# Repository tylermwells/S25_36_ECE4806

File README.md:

# S25-36-ECE4806
This is a repository to collaborate with schematic drawings, information, etc.

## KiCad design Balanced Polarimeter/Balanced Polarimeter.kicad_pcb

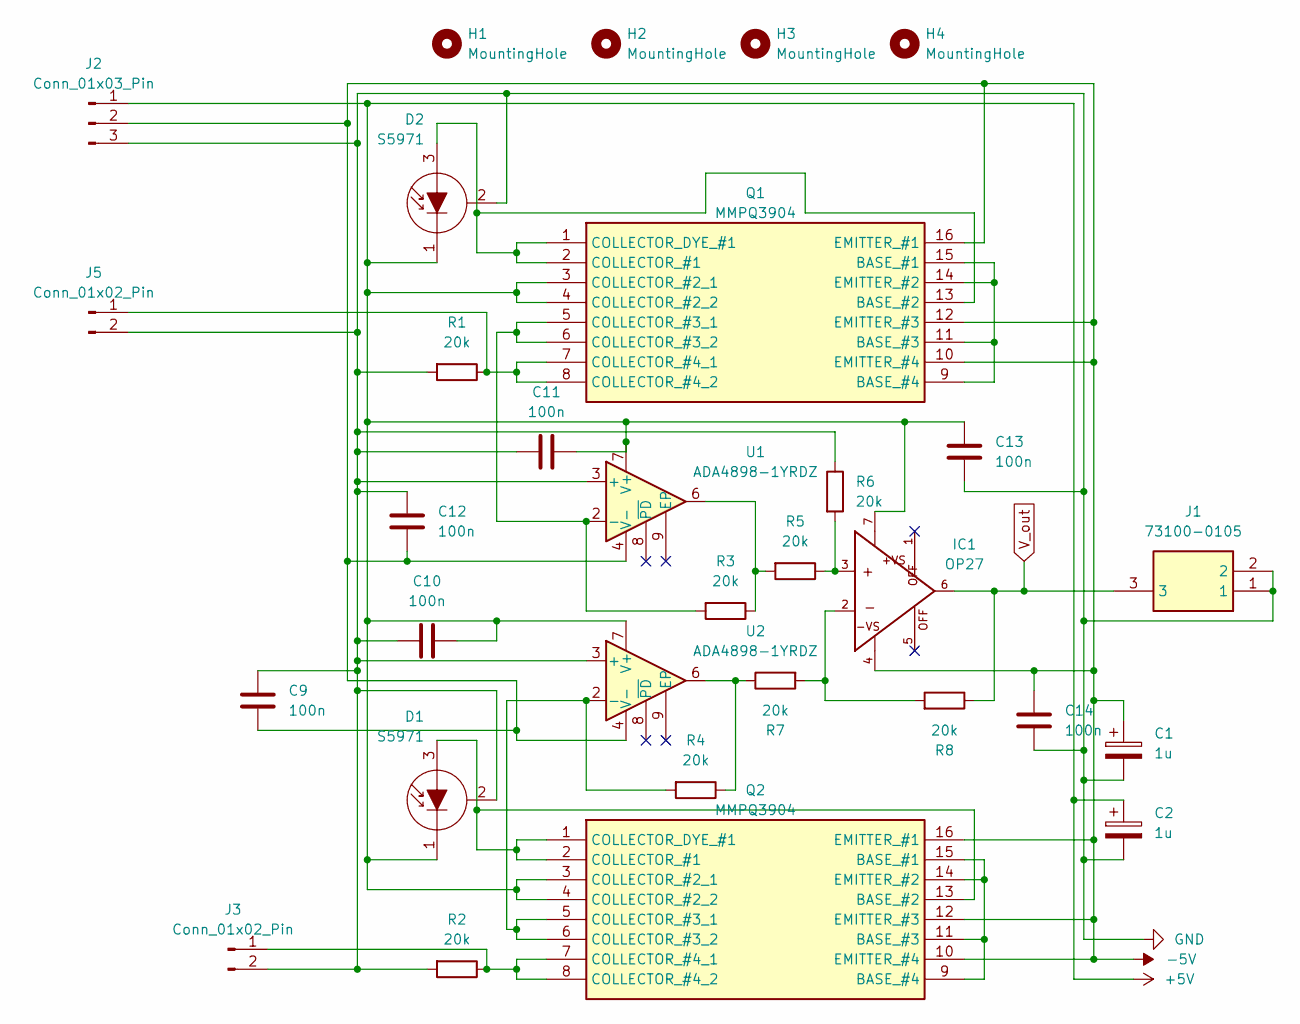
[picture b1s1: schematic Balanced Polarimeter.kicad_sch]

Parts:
C1, C2: 1u; CP_Radial_D5.0mm_P2.50mm
C9, C10, C11, C12, C13, C14: 100n; C_Disc_D3.0mm_W1.6mm_P2.50mm
D1, D2: S5971; TO-18-3
H1, H2, H3, H4: MountingHole; MountingHole_2.1mm
IC1: OP27; DIL08
J1: 73100-0105; Mouser Part Number 538-73100-0105
J2: Conn_01x03_Pin; FanPinHeader_1x03_P2.54mm_Vertical
J3, J5: Conn_01x02_Pin; PinHeader_1x02_P2.54mm_Vertical
Q1, Q2: MMPQ3904; SOIC127P600X175-16N; Mouser Part Number 512-MMPQ3904
R1, R2, R3, R4, R5, R6, R7, R8: 20k; R_Axial_DIN0207_L6.3mm_D2.5mm_P10.16mm_Horizontal
U1, U2: ADA4898-1YRDZ; SOIC-8-1EP_3.9x4.9mm_P1.27mm_EP2.29x3mm

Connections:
+5V: C2.1, C10.1, C11.1, C13.1, D1.1 (K), D2.1 (K), IC1.7, J2.1, Q1.3 (COLLECTOR_#2_1), Q1.4 (COLLECTOR_#2_2), Q2.3 (COLLECTOR_#2_1), Q2.4 (COLLECTOR_#2_2), U1.7 (V+), U2.7 (V+)
-5V: C1.1, C9.2, C12.2, C14.1, IC1.4, J2.2, Q1.10 (EMITTER_#4), Q1.12 (EMITTER_#3), Q1.16 (EMITTER_#1), Q2.10 (EMITTER_#4), Q2.12 (EMITTER_#3), Q2.16 (EMITTER_#1), U1.4 (V-), U2.4 (V-)
GND: C1.2, C2.2, C9.1, C10.2, C11.2, C12.1, C13.2, C14.2, D1.2 (C), D2.2 (C), J1.1, J1.2, J2.3, J3.2, J5.2, R1.2, R2.2, R6.1, U1.3 (+), U2.3 (+)
unnamed: D1.3 (A), Q2.1 (COLLECTOR_DYE_#1), Q2.2 (COLLECTOR_#1), Q2.13 (BASE_#2)
unnamed: D2.3 (A), Q1.1 (COLLECTOR_DYE_#1), Q1.2 (COLLECTOR_#1), Q1.13 (BASE_#2)
unnamed: IC1.2, R7.2, R8.2
unnamed: IC1.3, R5.1, R6.2
unnamed: J3.1, Q2.7 (COLLECTOR_#4_1), Q2.8 (COLLECTOR_#4_2), R2.1
unnamed: J5.1, Q1.7 (COLLECTOR_#4_1), Q1.8 (COLLECTOR_#4_2), R1.1
unnamed: Q1.9 (BASE_#4), Q1.11 (BASE_#3), Q1.14 (EMITTER_#2), Q1.15 (BASE_#1)
unnamed: Q1.5 (COLLECTOR_#3_1), Q1.6 (COLLECTOR_#3_2), R3.2, U1.2 (-)
unnamed: Q2.9 (BASE_#4), Q2.11 (BASE_#3), Q2.14 (EMITTER_#2), Q2.15 (BASE_#1)
unnamed: Q2.5 (COLLECTOR_#3_1), Q2.6 (COLLECTOR_#3_2), R4.2, U2.2 (-)
unnamed: R3.1, R5.2, U1.6
unnamed: R4.1, R7.1, U2.6
V_out: IC1.6, J1.3, R8.1

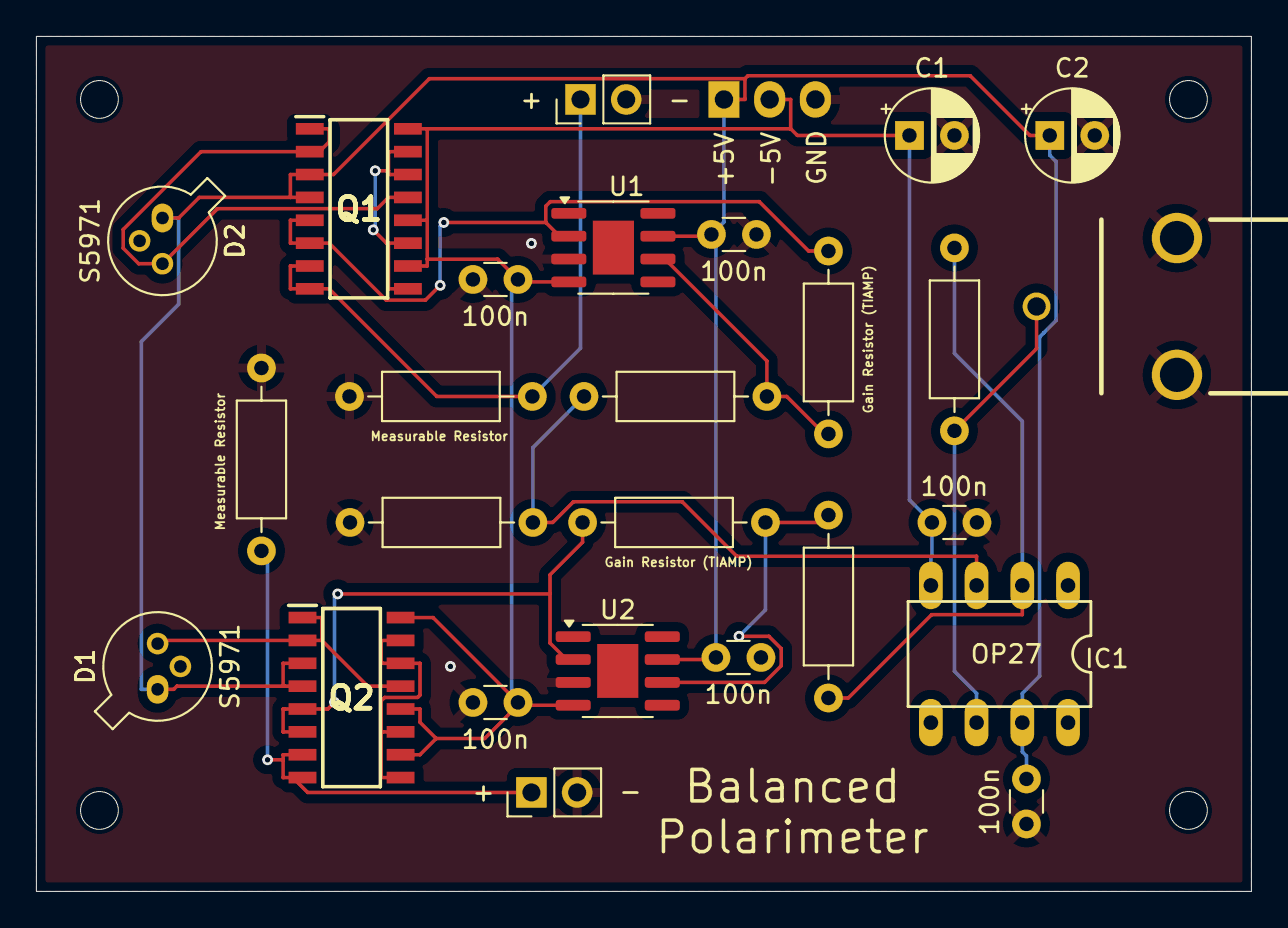
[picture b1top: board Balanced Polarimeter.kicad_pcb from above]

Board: 2 copper layers, 67.5 x 47.5 mm, 31 parts (0 on the bottom side), 16 nets.

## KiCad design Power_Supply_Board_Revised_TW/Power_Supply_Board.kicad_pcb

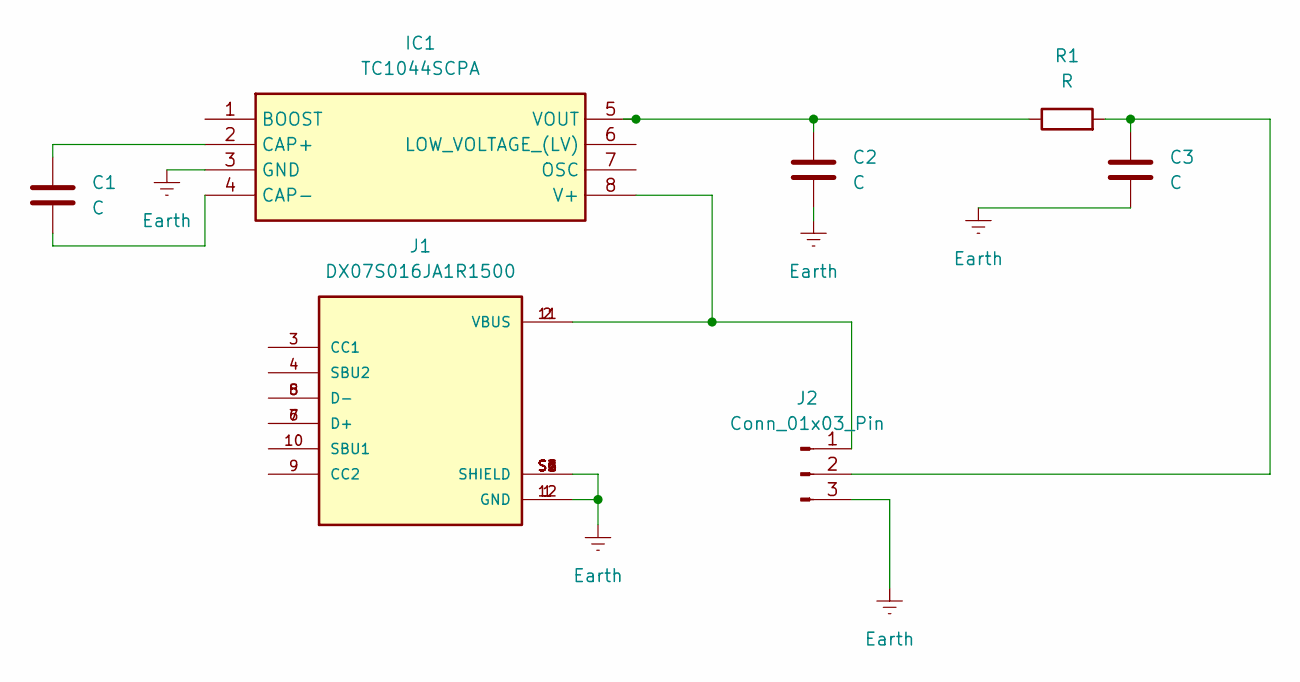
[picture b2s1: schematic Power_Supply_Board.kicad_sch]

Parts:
C1, C2: C; C_Rect_L7.0mm_W6.0mm_P5.00mm
C3: C; C_Rect_L16.5mm_W11.8mm_P15.00mm_MKT
IC1: TC1044SCPA; DIP762W56P254L950H508Q8N; Mouser Part Number 579-TC1044SCPA
J1: DX07S016JA1R1500; JAE_DX07S016JA1R1500; PARTREV 1
J2: Conn_01x03_Pin; PinHeader_1x03_P2.54mm_Vertical
R1: R; R_Axial_DIN0207_L6.3mm_D2.5mm_P10.16mm_Horizontal

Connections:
Earth: C2.2, C3.2, IC1.3 (GND), J1.1 (GND), J1.12 (GND), J1.S1 (SHIELD), J1.S2 (SHIELD), J1.S3 (SHIELD), J1.S4 (SHIELD), J1.S5 (SHIELD), J1.S6 (SHIELD), J2.3
unnamed: C1.1, IC1.2 (CAP+)
unnamed: C1.2, IC1.4 (CAP-)
unnamed: IC1.8 (V+), J1.2 (VBUS), J1.11 (VBUS), J2.1
unnamed: C2.1, IC1.5 (VOUT), R1.1
unnamed: J1.6 (D+), J1.7 (D+)
unnamed: J1.5 (D-), J1.8 (D-)
unnamed: C3.1, J2.2, R1.2

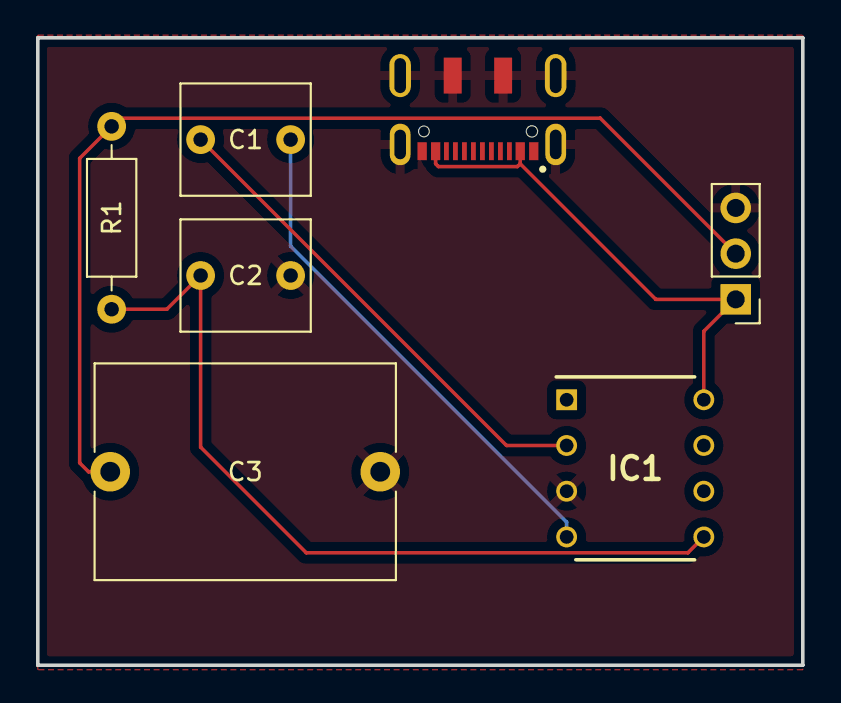
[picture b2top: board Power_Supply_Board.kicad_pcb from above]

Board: 2 copper layers, 42.5 x 34.9 mm, 7 parts (0 on the bottom side), 8 nets.

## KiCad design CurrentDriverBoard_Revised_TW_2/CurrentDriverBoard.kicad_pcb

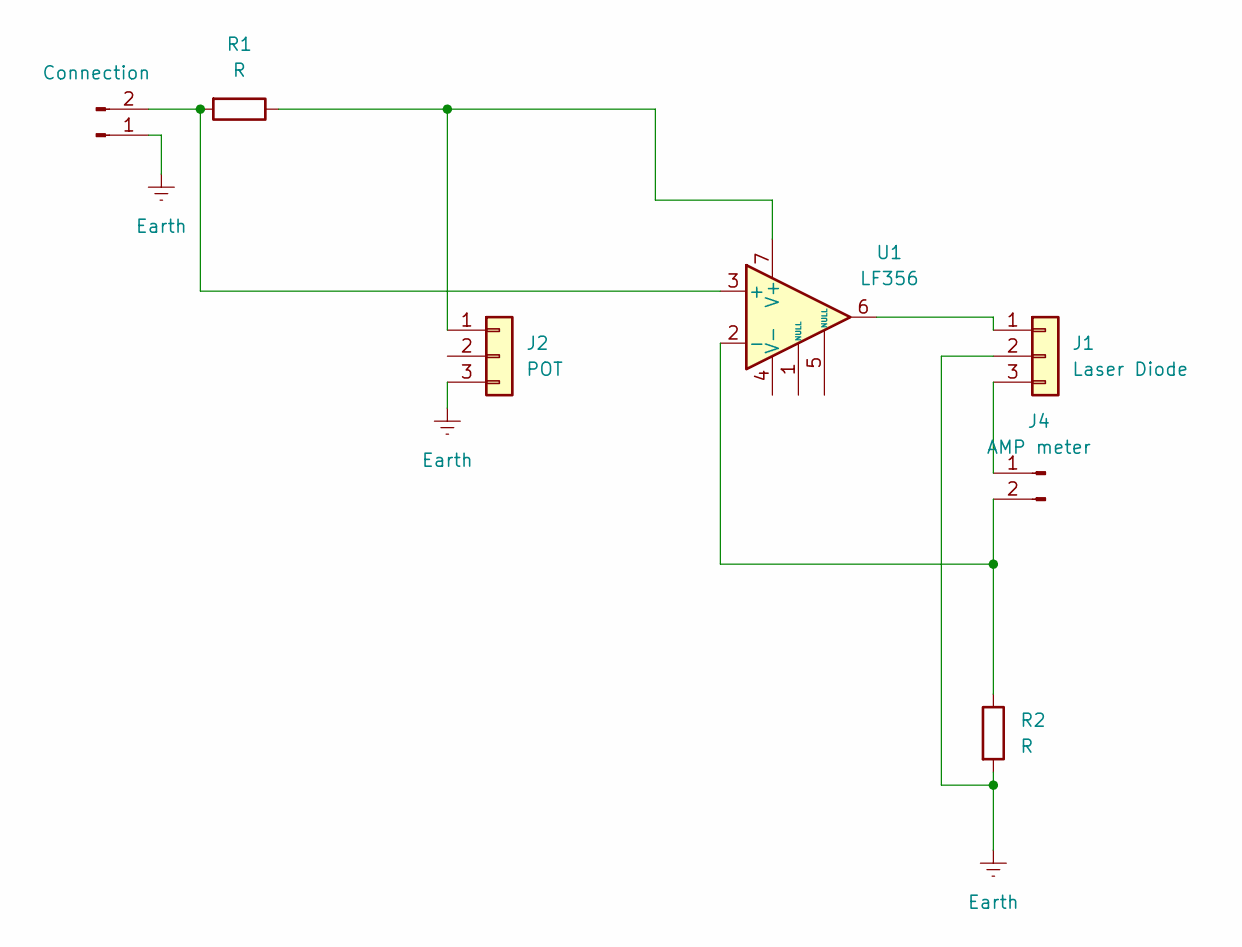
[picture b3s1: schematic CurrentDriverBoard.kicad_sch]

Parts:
J1: Laser Diode; PinHeader_1x03_P2.54mm_Vertical
J2: POT; PinHeader_1x03_P2.54mm_Vertical
J3: Connection; PinHeader_1x02_P2.54mm_Vertical
J4: AMP meter; PinHeader_1x02_P2.54mm_Vertical
R1, R2: R; R_Axial_DIN0207_L6.3mm_D2.5mm_P10.16mm_Horizontal
U1: LF356; DIP794W53P254L959H508Q8N

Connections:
Earth: J1.2, J2.3, J3.1, R2.2
unnamed: J1.1, U1.6
unnamed: J1.3, J4.1
unnamed: J2.1, R1.1, U1.7 (V+)
unnamed: J3.2, R1.2, U1.3 (+)
unnamed: J4.2, R2.1, U1.2 (-)

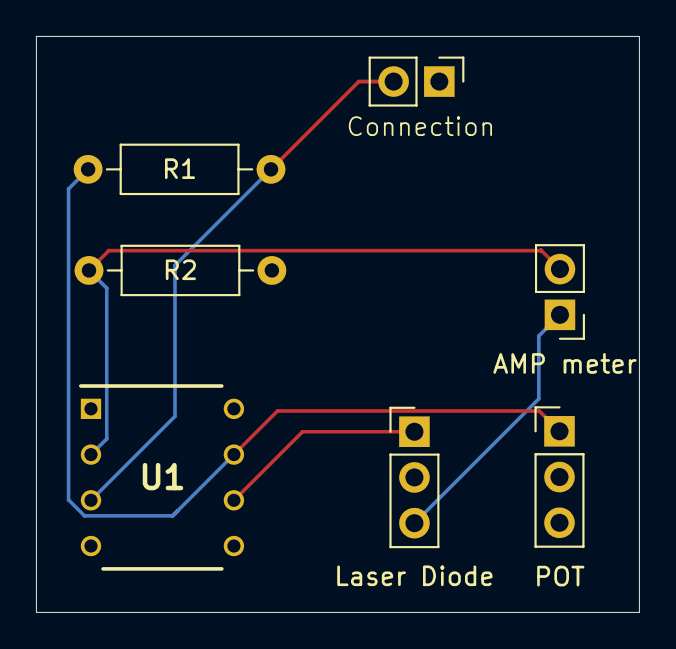
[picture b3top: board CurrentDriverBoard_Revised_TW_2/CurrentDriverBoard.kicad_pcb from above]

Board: 2 copper layers, 33.5 x 32.0 mm, 7 parts (0 on the bottom side), 6 nets.

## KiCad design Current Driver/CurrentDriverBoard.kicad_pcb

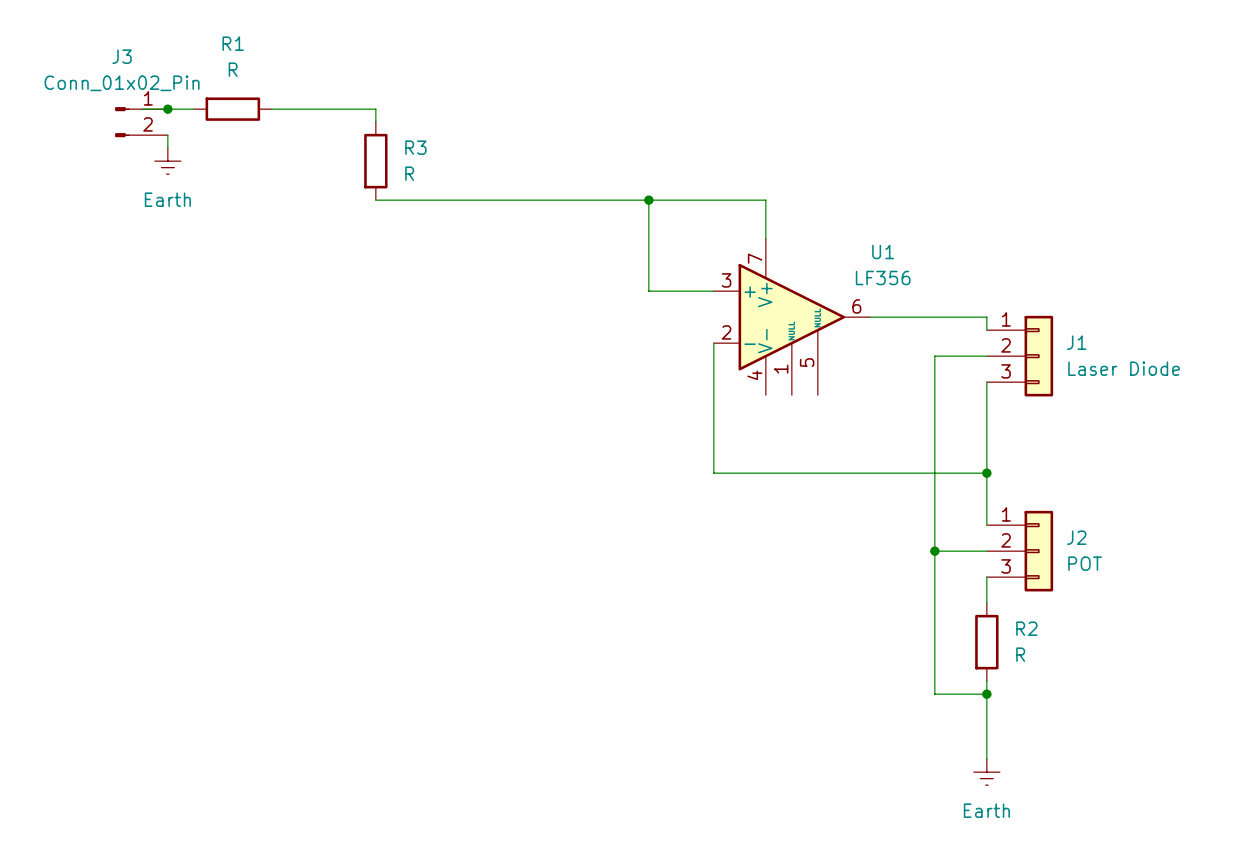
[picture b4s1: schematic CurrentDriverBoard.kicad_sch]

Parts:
J1: Laser Diode; PinHeader_1x03_P2.54mm_Vertical
J2: POT; PinHeader_1x03_P2.54mm_Vertical
J3: Conn_01x02_Pin; PinHeader_1x02_P2.54mm_Vertical
R1, R2, R3: R; R_Axial_DIN0207_L6.3mm_D2.5mm_P10.16mm_Horizontal
U1: LF356; DIP794W53P254L959H508Q8N

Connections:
Earth: J1.2, J2.2, J3.2, R2.2
unnamed: J1.1, U1.6
unnamed: J1.3, J2.1, U1.2 (-)
unnamed: J2.3, R2.1
unnamed: J3.1, R1.2
unnamed: R1.1, R3.1
unnamed: R3.2, U1.3 (+), U1.7 (V+)

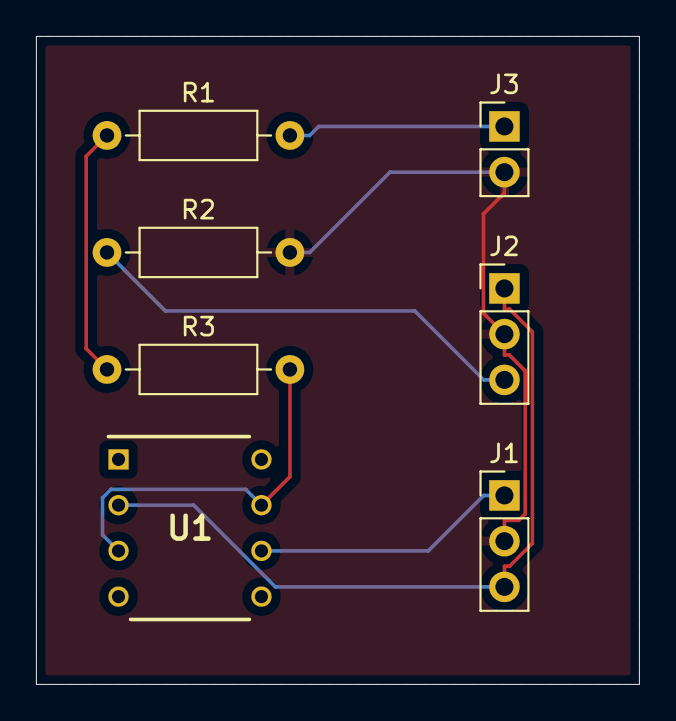
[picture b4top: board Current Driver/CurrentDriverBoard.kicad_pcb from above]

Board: 2 copper layers, 33.5 x 36.0 mm, 7 parts (0 on the bottom side), 7 nets.

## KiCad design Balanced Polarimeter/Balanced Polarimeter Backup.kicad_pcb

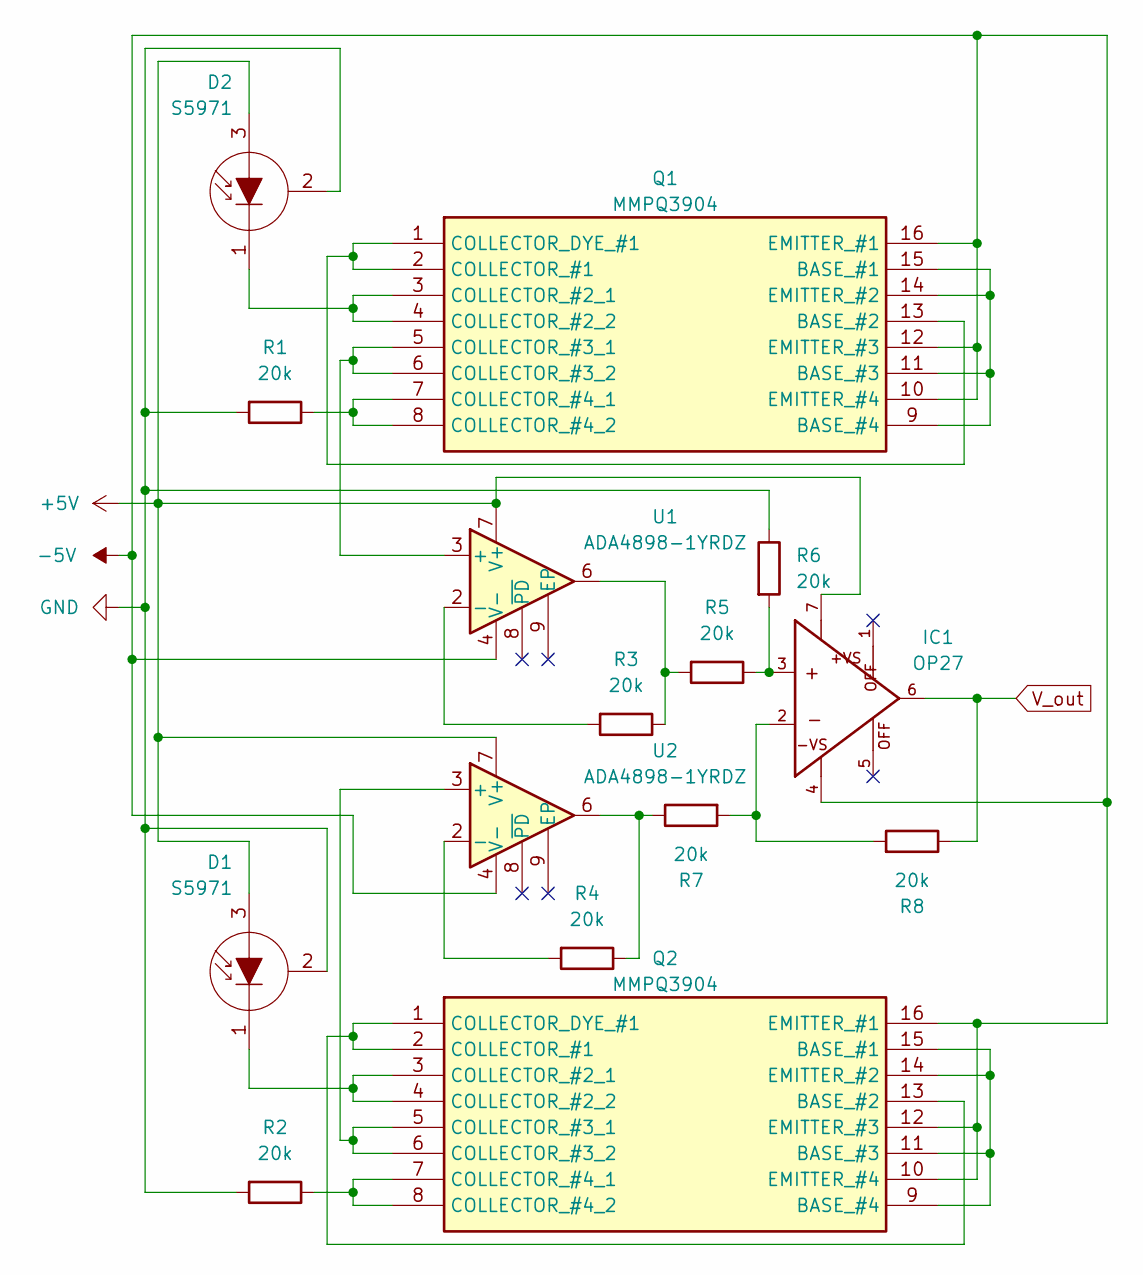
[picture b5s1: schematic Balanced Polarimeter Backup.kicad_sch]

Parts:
D1, D2: S5971; TO-18-3
IC1: OP27; DIL08
Q1, Q2: MMPQ3904; SOIC127P600X175-16N; Mouser Part Number 512-MMPQ3904
R1, R2, R3, R4, R5, R6, R7, R8: 20k; R_Axial_DIN0207_L6.3mm_D2.5mm_P10.16mm_Horizontal
U1, U2: ADA4898-1YRDZ; SOIC-8-1EP_3.9x4.9mm_P1.27mm_EP2.29x3mm

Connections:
+5V: D1.3 (A), D2.3 (A), IC1.7, U1.7 (V+), U2.7 (V+)
-5V: IC1.4, Q1.10 (EMITTER_#4), Q1.12 (EMITTER_#3), Q1.16 (EMITTER_#1), Q2.10 (EMITTER_#4), Q2.12 (EMITTER_#3), Q2.16 (EMITTER_#1), U1.4 (V-), U2.4 (V-)
GND: D1.2 (C), D2.2 (C), R1.2, R2.2, R6.1
unnamed: D1.1 (K), Q2.3 (COLLECTOR_#2_1), Q2.4 (COLLECTOR_#2_2)
unnamed: D2.1 (K), Q1.3 (COLLECTOR_#2_1), Q1.4 (COLLECTOR_#2_2)
unnamed: IC1.2, R7.2, R8.2
unnamed: IC1.3, R5.1, R6.2
unnamed: Q1.9 (BASE_#4), Q1.11 (BASE_#3), Q1.14 (EMITTER_#2), Q1.15 (BASE_#1)
unnamed: Q1.1 (COLLECTOR_DYE_#1), Q1.2 (COLLECTOR_#1), Q1.13 (BASE_#2)
unnamed: Q1.5 (COLLECTOR_#3_1), Q1.6 (COLLECTOR_#3_2), U1.3 (+)
unnamed: Q1.7 (COLLECTOR_#4_1), Q1.8 (COLLECTOR_#4_2), R1.1
unnamed: Q2.9 (BASE_#4), Q2.11 (BASE_#3), Q2.14 (EMITTER_#2), Q2.15 (BASE_#1)
unnamed: Q2.1 (COLLECTOR_DYE_#1), Q2.2 (COLLECTOR_#1), Q2.13 (BASE_#2)
unnamed: Q2.5 (COLLECTOR_#3_1), Q2.6 (COLLECTOR_#3_2), U2.3 (+)
unnamed: Q2.7 (COLLECTOR_#4_1), Q2.8 (COLLECTOR_#4_2), R2.1
unnamed: R3.1, R5.2, U1.6
unnamed: R4.1, R7.1, U2.6
unnamed: R3.2, U1.2 (-)
unnamed: R4.2, U2.2 (-)
V_out: IC1.6, R8.1

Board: 2 copper layers, 15 parts (0 on the bottom side), 20 nets, no tracks yet.

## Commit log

2025-01-10 Adding LTSPICE Folder with schematic
2025-01-10 Balanced Polarimeter
    Created the balanced polarimeter project folder for PCB
2025-01-10 Balanced Polarimeter
2025-01-21 Added SS and TA
2025-01-23 Next revision
    Rewired all powers to a single node and swapped the op amp for an op27
2025-01-23 PCB Start Design
    Edited the naming of some components and created a PCB to layout. It's still missing the BNC connector for now
2025-01-23 Cleanup
    Removed the "Backup" files
2025-01-24 Added BNC
2025-01-24 Simple Updates
2025-01-30 Added GND Layer and 2mm Mount Holes
2025-01-30 Added Part List
2025-01-31 Updating Parts List
    Updating Parts List with links of what we need
2025-01-31 Adding AJs current driver to the repository
2025-02-03 Adding Power Supply Driver and Master Parts list to the repository. More updates to come soon because we need to add resistors.
2025-02-03 Added 1% resistors to Master Parts List
2025-02-03 BNC Revision
2025-02-03 Updating Associated Files. Some files can only be opened in Linux. Sorry Windows Users :P
2025-02-21 Revised BP
2025-02-22 Revised Wiring
2025-02-25 BNC Grounding
2025-02-25 Renamed the folders
2025-02-27 Changed H2 and H4 location
2025-02-28 Adding updated PCBs
2025-02-28 Adding Gerbers and Drills to repos
2025-03-23 Added Caps and Bias Change
2025-03-23 Nothing much
2025-03-24 Fixed the board because there were untraced pieces
2025-04-08 Added caps to schematic
2025-04-08 Changed the cap types
2025-04-11 Finalized the PCB Design
2025-05-01 Updated the LTSPICE
2025-05-02 Updated Final Board
